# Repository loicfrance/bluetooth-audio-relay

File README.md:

# bluetooth-audio-relay
Audio Bluetooth to audio jack module

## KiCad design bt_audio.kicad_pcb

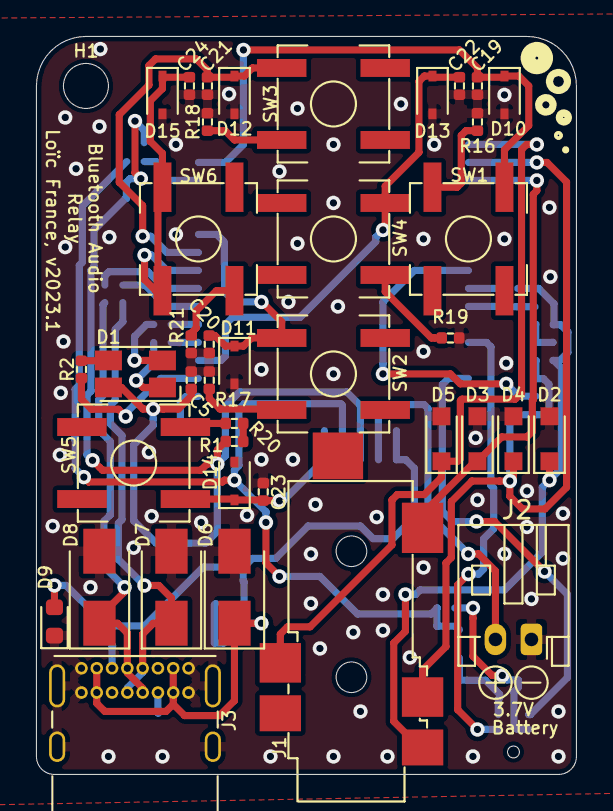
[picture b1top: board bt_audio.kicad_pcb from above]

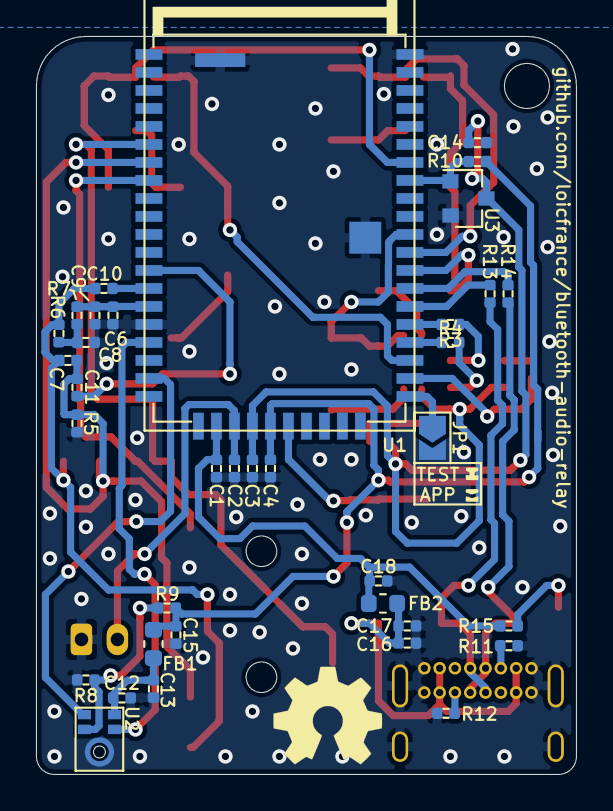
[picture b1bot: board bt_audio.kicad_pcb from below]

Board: 2 copper layers, 30.0 x 41.0 mm, 77 parts (37 on the bottom side), 46 nets.

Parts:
C1, C2, C6, C8, C9, C18: 1u; C_0402_1005Metric
C3, C4, C5, C13, C14, C15, C16, C17: 100n; C_0402_1005Metric
C7, C12: 220p; C_0402_1005Metric
C10, C11: 47n; C_0402_1005Metric
C19, C20, C21, C22, C23, C24: 15p; C_0402_1005Metric
D1: LED_RGBA; LED_Avago_PLCC4_3.2x2.8mm_CW
D2, D3, D4, D5: PESD5V0S1BA; D_SOD-323_HandSoldering
D6, D7, D8: SMBJ10CA-TR; D_SMA
D9: GREEN; LED_0603_1608Metric
D10, D11, D12, D13, D14, D15: PESD5V0S1BA; D_SOD-323
FB1: 120R; L_0603_1608Metric
FB2: 100R; L_0603_1608Metric
H1: MountingHole; MountingHole_2.5mm
J1: AudioJack4_Ground; SJ-43516-SMT
J2: Conn_01x02; JST_PH_S2B-PH-K_1x02_P2.00mm_Horizontal
J3: USB_C_Receptacle_USB2.0; USB_C_Receptacle_GCT_USB4085
JP1: SYS_CFG; SolderJumper-2_P1.3mm_Open_TrianglePad1.0x1.5mm
LOGO1: Logo_Open_Hardware_Large; openhardware_logo
R1, R2, R3, R4, R13, R14, R16, R17, R18, R19, R20, R21: 0; R_0402_1005Metric
R5: 2.2k; R_0402_1005Metric
R6, R7, R15: 1k; R_0402_1005Metric
R8, R9, R10: 4.7k; R_0402_1005Metric
R11, R12: 5.1k; R_0402_1005Metric
SW1, SW2, SW3, SW4, SW5, SW6: EVP-BV2C1L000; tactile_switch
U1: MC_BM83
U2: SPH0641LU4H-1
U3: MCP111-300E; SOT-23

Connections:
/ADAP_IN: C1.1, C18.1, FB2.1, R15.1, U1.22
/AOHPL: D3.1, J1.T, U1.8
/AOHPM: C7.1, C11.1, D4.1, J1.R2, R5.1, U1.7
/AOHPR: D5.1, J1.R1, U1.6
/BAT_IN: C2.1, J2.2, U1.23
/DMIC1_L: U1.19, U2.1
/DMIC_CLK: U1.17, U2.4
/FWD: C19.1, D10.1, SW1.2, U1.44
/JACK_OUT_MIC: C7.2, C10.1, D2.1, J1.S, R6.2
/LED1: R2.2, U1.32
/LED2: R4.2, U1.34
/MFB PWR/push_value: R1.1, R20.2
/MFB_PWR: C23.1, D14.1, SW5.2, U1.26
/MIC_BIAS: C6.1, C9.2, R7.1, U1.15
/MIC_N1: C11.2, U1.13
/MIC_P1: C10.2, U1.14
/PLAY_PAUSE: C22.1, D13.1, SW4.2, U1.33
/PWM_LED: R3.2, U1.35
/REV: C24.1, D15.1, SW6.2, U1.38
/RST_N: R10.1, U1.43, U3.1
/SYS_CFG: JP1.1, U1.31
/SYS_PWR: C3.1, C5.2, C14.1, D1.2, R1.2, U1.24, U3.3
/USB_DM: R13.2, U1.36
/USB_DP: R14.2, U1.37
/VDD_IO: C4.1, C15.1, FB1.1, R9.1, R10.2, U1.25
/VOL_DOWN: C20.1, D11.1, SW2.2, U1.40
/VOL_UP: C21.1, D12.1, SW3.2, U1.39
GND: C1.2, C2.2, C3.2, C4.2, C5.1, C6.2, C8.1, C9.1, C12.2, C13.2, C14.2, C15.2, C16.2, C17.2, C18.2, C19.2, C20.2, C21.2, C22.2, C23.2, C24.2, D2.2, D3.2, D4.2, D5.2, D6.2, D7.2, D8.2, D9.1, D10.2, D11.2, D12.2, D13.2, D14.2, D15.2, J2.1, J3.A1, J3.A12, J3.B1, J3.B12, J3.S1, JP1.2, R5.2, R8.2, R11.1, R12.1, R16.2, R17.2, R18.2, R19.2, R21.2, U1.16, U1.50, U1.56, U1.57, U2.3, U3.2
unnamed: C8.2, R6.1, R7.2
unnamed: C12.1, C13.1, FB1.2, U2.5
unnamed: C16.1, C17.1, D6.1, FB2.2, J3.A4, J3.A9, J3.B4, J3.B9
unnamed: D1.1, R4.1
unnamed: D1.3, R2.1
unnamed: D1.4, R3.1
unnamed: D7.1, J3.A7, J3.B7, R13.1
unnamed: D8.1, J3.A6, J3.B6, R14.1
unnamed: D9.2, R15.2
unnamed: J3.A5, R11.2
unnamed: J3.B5, R12.2
unnamed: R8.1, R9.2, U2.2
unnamed: R16.1, SW1.1
unnamed: R17.1, SW2.1
unnamed: R18.1, SW3.1
unnamed: R19.1, SW4.1
unnamed: R20.1, SW5.1
unnamed: R21.1, SW6.1

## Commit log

2023-03-20 Add Project v2023.1
2023-03-20 add git url on pcb, add gitignore
